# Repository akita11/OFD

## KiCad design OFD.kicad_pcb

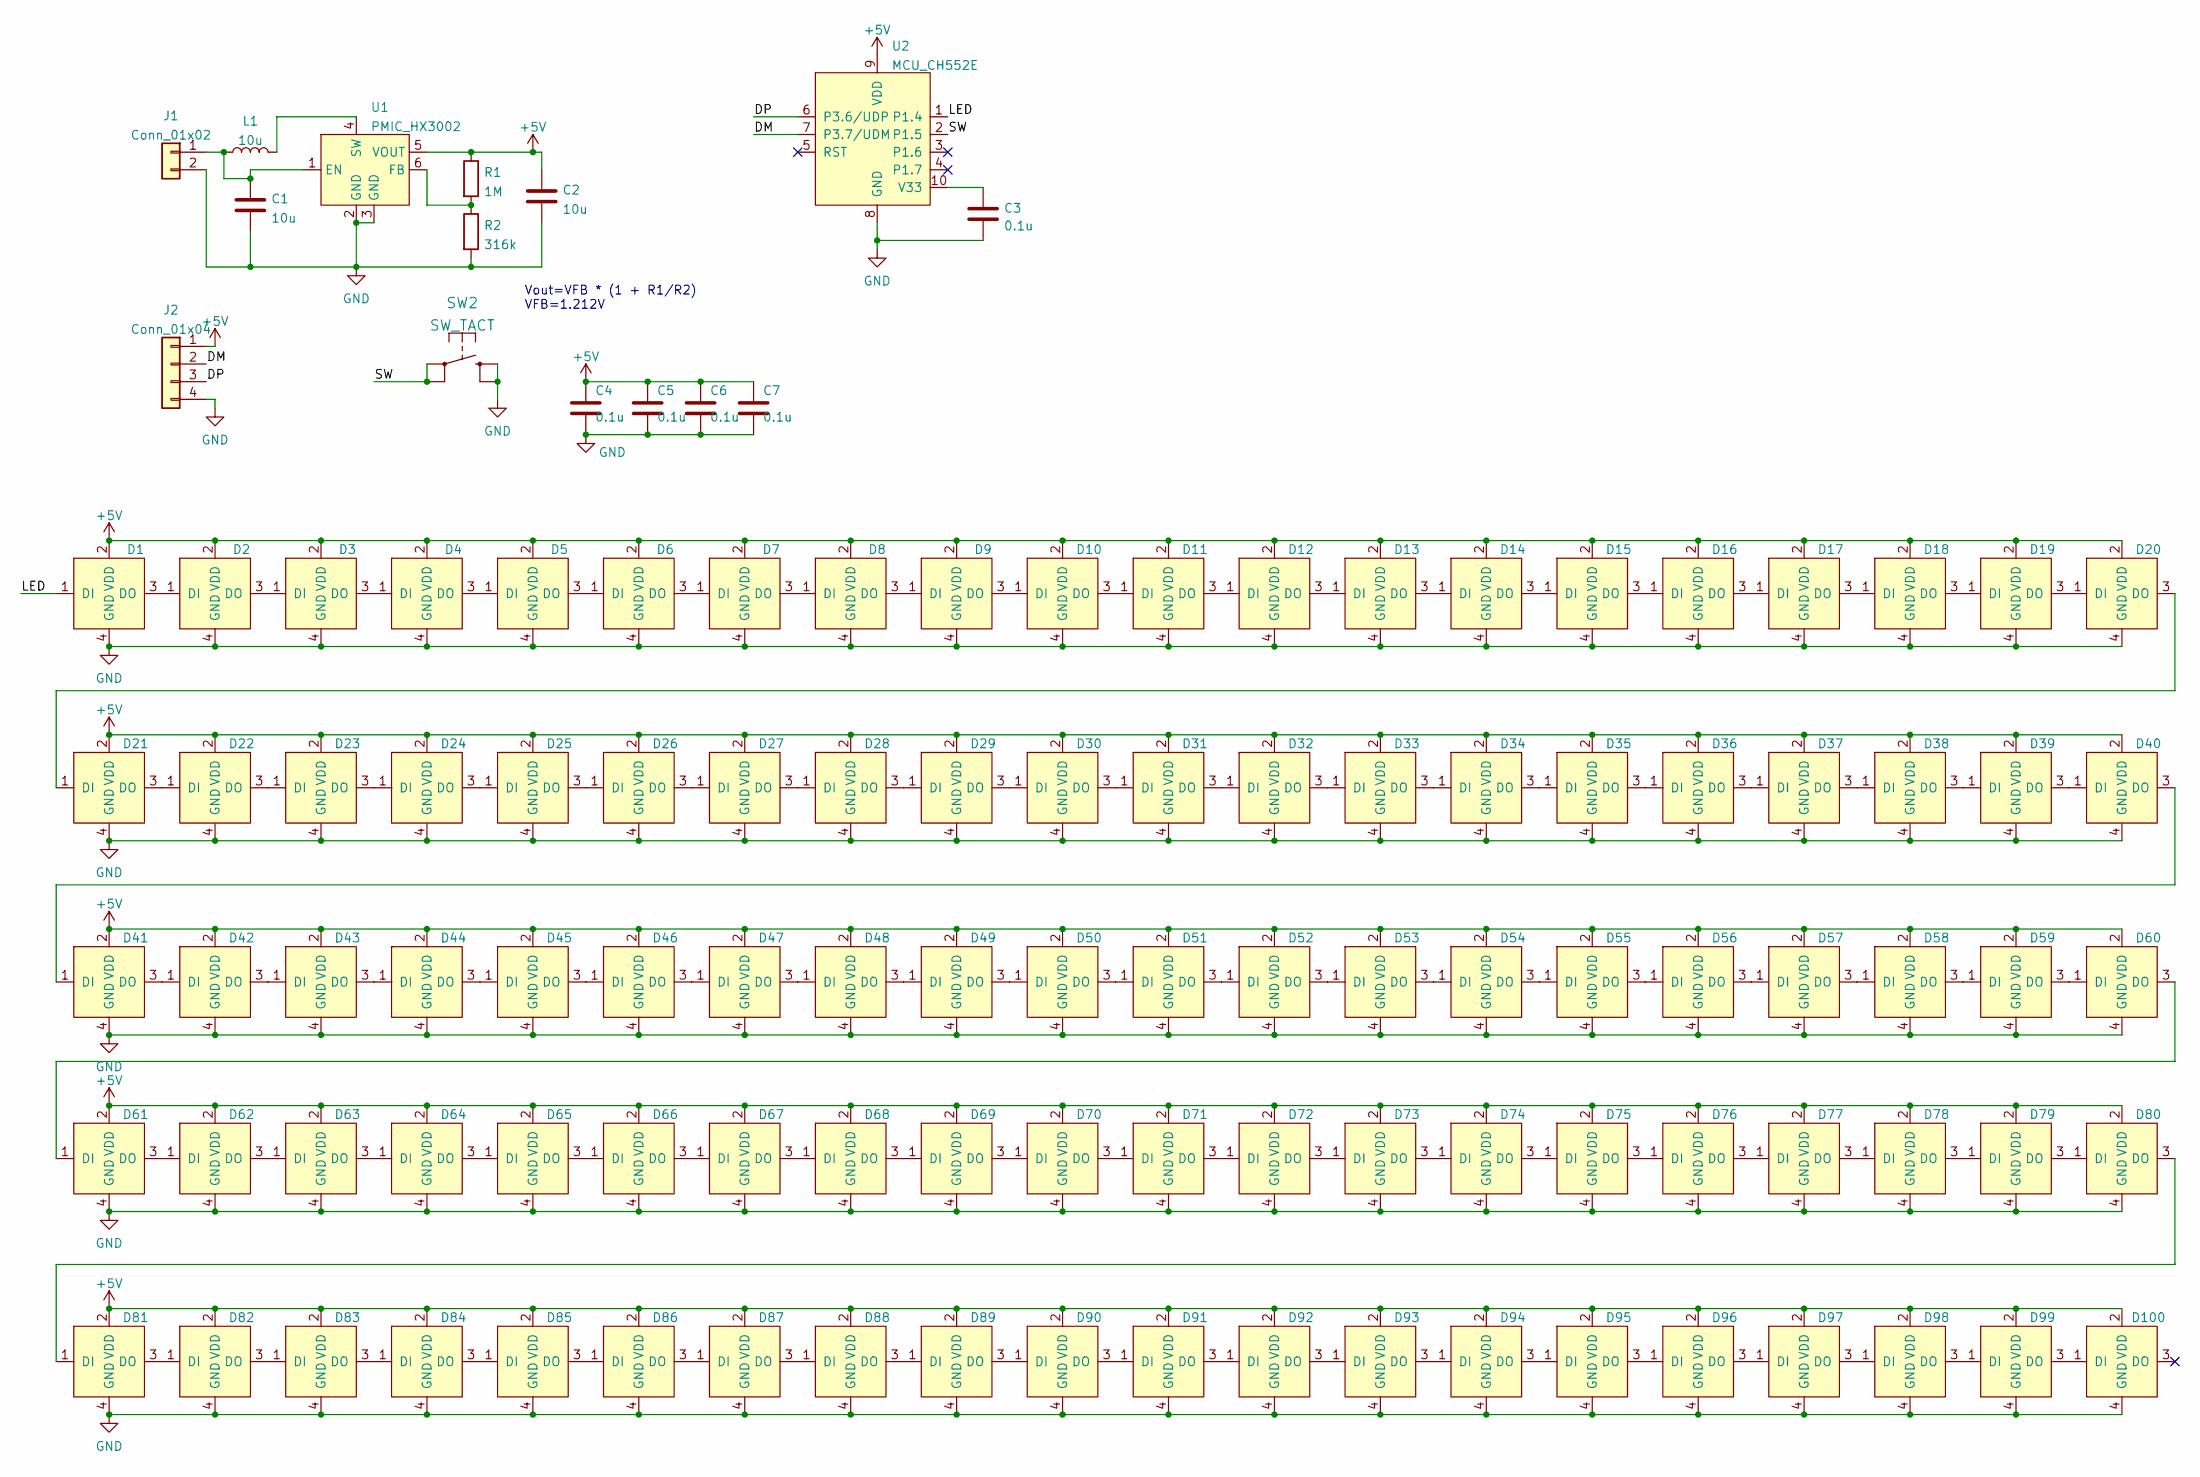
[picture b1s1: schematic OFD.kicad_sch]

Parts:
C1, C2: 10u; C_0603_1608Metric; LCSC C109454
C3, C5, C6, C7: 0.1u; C_0603_1608Metric; LCSC C14663
C4: 0.1u; C_0603_1608Metric
D1, D2, D3, D4, D5, D6, D7, D8, D9, D10, D11, D12, D13, D14, D15, D16, D17, D18, D19, D20, D21, D22, D23, D24, D25, D26, D27, D28, D29, D30, D31, D32, D33, D34, D35, D36, D37, D38, D39, D40, D41, D42, D43, D44, D45, D46, D47, D48, D49, D50, D51, D52, D53, D54, D55, D56, D57, D58, D59, D60, D61, D62, D63, D64, D65, D66, D67, D68, D69, D70, D71, D72, D73, D74, D75, D76, D77, D78, D79, D80, D81, D82, D83, D84, D85, D86, D87, D88, D89, D90, D91, D92, D93, D94, D95, D96, D97, D98, D99, D100: LED_SK6812side; LED_SK6812SIDE_A; LCSC C5378721
J1: Conn_01x02; JST_PH2_SMD; LCSC C295747
J2: Conn_01x04; PinSocket_1x04_P2.54mm_Vertical
L1: 10u; L_SMD_3x3mm; LCSC C6364790
R1: 1M; R_0603_1608Metric; LCSC C318138
R2: 316k; R_0603_1608Metric; LCSC C100961
SW2: SW_TACT; SW_SPST_B3S-1000; LCSC C2905128
U1: PMIC_HX3002; SOT-23-6; LCSC C172353
U2: MCU_CH552E; TSSOP-10_3x3mm_P0.5mm; LCSC C967938

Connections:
+5V: C2.1, C4.1, C5.1, C6.1, C7.1, D1.2 (VDD), D2.2 (VDD), D3.2 (VDD), D4.2 (VDD), D5.2 (VDD), D6.2 (VDD), D7.2 (VDD), D8.2 (VDD), D9.2 (VDD), D10.2 (VDD), D11.2 (VDD), D12.2 (VDD), D13.2 (VDD), D14.2 (VDD), D15.2 (VDD), D16.2 (VDD), D17.2 (VDD), D18.2 (VDD), D19.2 (VDD), D20.2 (VDD), D21.2 (VDD), D22.2 (VDD), D23.2 (VDD), D24.2 (VDD), D25.2 (VDD), D26.2 (VDD), D27.2 (VDD), D28.2 (VDD), D29.2 (VDD), D30.2 (VDD), D31.2 (VDD), D32.2 (VDD), D33.2 (VDD), D34.2 (VDD), D35.2 (VDD), D36.2 (VDD), D37.2 (VDD), D38.2 (VDD), D39.2 (VDD), D40.2 (VDD), D41.2 (VDD), D42.2 (VDD), D43.2 (VDD), D44.2 (VDD), D45.2 (VDD), D46.2 (VDD), D47.2 (VDD), D48.2 (VDD), D49.2 (VDD), D50.2 (VDD), D51.2 (VDD), D52.2 (VDD), D53.2 (VDD), D54.2 (VDD), D55.2 (VDD), D56.2 (VDD), D57.2 (VDD), D58.2 (VDD), D59.2 (VDD), D60.2 (VDD), D61.2 (VDD), D62.2 (VDD), D63.2 (VDD), D64.2 (VDD), D65.2 (VDD), D66.2 (VDD), D67.2 (VDD), D68.2 (VDD), D69.2 (VDD), D70.2 (VDD), D71.2 (VDD), D72.2 (VDD), D73.2 (VDD), D74.2 (VDD), D75.2 (VDD), D76.2 (VDD), D77.2 (VDD), D78.2 (VDD), D79.2 (VDD), D80.2 (VDD), D81.2 (VDD), D82.2 (VDD), D83.2 (VDD), D84.2 (VDD), D85.2 (VDD), D86.2 (VDD), D87.2 (VDD), D88.2 (VDD), D89.2 (VDD), D90.2 (VDD), D91.2 (VDD), D92.2 (VDD), D93.2 (VDD), D94.2 (VDD), D95.2 (VDD), D96.2 (VDD), D97.2 (VDD), D98.2 (VDD), D99.2 (VDD), D100.2 (VDD), J2.1, R1.1, U1.5 (VOUT), U2.9 (VDD)
/DM: J2.2, U2.7 (P3.7/UDM)
/DP: J2.3, U2.6 (P3.6/UDP)
/LED: D1.1 (DI), U2.1 (P1.4)
/SW: SW2.1, U2.2 (P1.5); also elsewhere on the board
GND: C1.2, C2.2, C3.2, C4.2, C5.2, C6.2, C7.2, D1.4 (GND), D2.4 (GND), D3.4 (GND), D4.4 (GND), D5.4 (GND), D6.4 (GND), D7.4 (GND), D8.4 (GND), D9.4 (GND), D10.4 (GND), D11.4 (GND), D12.4 (GND), D13.4 (GND), D14.4 (GND), D15.4 (GND), D16.4 (GND), D17.4 (GND), D18.4 (GND), D19.4 (GND), D20.4 (GND), D21.4 (GND), D22.4 (GND), D23.4 (GND), D24.4 (GND), D25.4 (GND), D26.4 (GND), D27.4 (GND), D28.4 (GND), D29.4 (GND), D30.4 (GND), D31.4 (GND), D32.4 (GND), D33.4 (GND), D34.4 (GND), D35.4 (GND), D36.4 (GND), D37.4 (GND), D38.4 (GND), D39.4 (GND), D40.4 (GND), D41.4 (GND), D42.4 (GND), D43.4 (GND), D44.4 (GND), D45.4 (GND), D46.4 (GND), D47.4 (GND), D48.4 (GND), D49.4 (GND), D50.4 (GND), D51.4 (GND), D52.4 (GND), D53.4 (GND), D54.4 (GND), D55.4 (GND), D56.4 (GND), D57.4 (GND), D58.4 (GND), D59.4 (GND), D60.4 (GND), D61.4 (GND), D62.4 (GND), D63.4 (GND), D64.4 (GND), D65.4 (GND), D66.4 (GND), D67.4 (GND), D68.4 (GND), D69.4 (GND), D70.4 (GND), D71.4 (GND), D72.4 (GND), D73.4 (GND), D74.4 (GND), D75.4 (GND), D76.4 (GND), D77.4 (GND), D78.4 (GND), D79.4 (GND), D80.4 (GND), D81.4 (GND), D82.4 (GND), D83.4 (GND), D84.4 (GND), D85.4 (GND), D86.4 (GND), D87.4 (GND), D88.4 (GND), D89.4 (GND), D90.4 (GND), D91.4 (GND), D92.4 (GND), D93.4 (GND), D94.4 (GND), D95.4 (GND), D96.4 (GND), D97.4 (GND), D98.4 (GND), D99.4 (GND), D100.4 (GND), J1.2, J2.4, R2.2, SW2.2, U1.2 (GND), U1.3 (GND), U2.8 (GND); also elsewhere on the board
unnamed: C1.1, J1.1, L1.1, U1.1 (EN)
unnamed: C3.1, U2.10 (V33)
unnamed: D1.3 (DO), D2.1 (DI)
unnamed: D2.3 (DO), D3.1 (DI)
unnamed: D3.3 (DO), D4.1 (DI)
unnamed: D4.3 (DO), D5.1 (DI)
unnamed: D5.3 (DO), D6.1 (DI)
unnamed: D6.3 (DO), D7.1 (DI)
unnamed: D7.3 (DO), D8.1 (DI)
unnamed: D8.3 (DO), D9.1 (DI)
unnamed: D9.3 (DO), D10.1 (DI)
unnamed: D10.3 (DO), D11.1 (DI)
unnamed: D11.3 (DO), D12.1 (DI)
unnamed: D12.3 (DO), D13.1 (DI)
unnamed: D13.3 (DO), D14.1 (DI)
unnamed: D14.3 (DO), D15.1 (DI)
unnamed: D15.3 (DO), D16.1 (DI)
unnamed: D16.3 (DO), D17.1 (DI)
unnamed: D17.3 (DO), D18.1 (DI)
unnamed: D18.3 (DO), D19.1 (DI)
unnamed: D19.3 (DO), D20.1 (DI)
unnamed: D20.3 (DO), D21.1 (DI)
unnamed: D21.3 (DO), D22.1 (DI)
unnamed: D22.3 (DO), D23.1 (DI)
unnamed: D23.3 (DO), D24.1 (DI)
unnamed: D24.3 (DO), D25.1 (DI)
unnamed: D25.3 (DO), D26.1 (DI)
unnamed: D26.3 (DO), D27.1 (DI)
unnamed: D27.3 (DO), D28.1 (DI)
unnamed: D28.3 (DO), D29.1 (DI)
unnamed: D29.3 (DO), D30.1 (DI)
unnamed: D30.3 (DO), D31.1 (DI)
unnamed: D31.3 (DO), D32.1 (DI)
unnamed: D32.3 (DO), D33.1 (DI)
unnamed: D33.3 (DO), D34.1 (DI)
unnamed: D34.3 (DO), D35.1 (DI)
unnamed: D35.3 (DO), D36.1 (DI)
unnamed: D36.3 (DO), D37.1 (DI)
unnamed: D37.3 (DO), D38.1 (DI)
unnamed: D38.3 (DO), D39.1 (DI)
unnamed: D39.3 (DO), D40.1 (DI)
unnamed: D40.3 (DO), D41.1 (DI)
unnamed: D41.3 (DO), D42.1 (DI)
unnamed: D42.3 (DO), D43.1 (DI)
unnamed: D43.3 (DO), D44.1 (DI)
unnamed: D44.3 (DO), D45.1 (DI)
unnamed: D45.3 (DO), D46.1 (DI)
unnamed: D46.3 (DO), D47.1 (DI)
unnamed: D47.3 (DO), D48.1 (DI)
unnamed: D48.3 (DO), D49.1 (DI)
unnamed: D49.3 (DO), D50.1 (DI)
unnamed: D50.3 (DO), D51.1 (DI)
unnamed: D51.3 (DO), D52.1 (DI)
unnamed: D52.3 (DO), D53.1 (DI)
unnamed: D53.3 (DO), D54.1 (DI)
unnamed: D54.3 (DO), D55.1 (DI)
unnamed: D55.3 (DO), D56.1 (DI)
unnamed: D56.3 (DO), D57.1 (DI)
unnamed: D57.3 (DO), D58.1 (DI)
unnamed: D58.3 (DO), D59.1 (DI)
unnamed: D59.3 (DO), D60.1 (DI)
unnamed: D60.3 (DO), D61.1 (DI)
unnamed: D61.3 (DO), D62.1 (DI)
unnamed: D62.3 (DO), D63.1 (DI)
unnamed: D63.3 (DO), D64.1 (DI)
unnamed: D64.3 (DO), D65.1 (DI)
unnamed: D65.3 (DO), D66.1 (DI)
unnamed: D66.3 (DO), D67.1 (DI)
unnamed: D67.3 (DO), D68.1 (DI)
unnamed: D68.3 (DO), D69.1 (DI)
unnamed: D69.3 (DO), D70.1 (DI)
unnamed: D70.3 (DO), D71.1 (DI)
unnamed: D71.3 (DO), D72.1 (DI)
unnamed: D72.3 (DO), D73.1 (DI)
unnamed: D73.3 (DO), D74.1 (DI)
unnamed: D74.3 (DO), D75.1 (DI)
unnamed: D75.3 (DO), D76.1 (DI)
unnamed: D76.3 (DO), D77.1 (DI)
unnamed: D77.3 (DO), D78.1 (DI)
unnamed: D78.3 (DO), D79.1 (DI)
unnamed: D79.3 (DO), D80.1 (DI)
unnamed: D80.3 (DO), D81.1 (DI)
unnamed: D81.3 (DO), D82.1 (DI)
unnamed: D82.3 (DO), D83.1 (DI)
unnamed: D83.3 (DO), D84.1 (DI)
unnamed: D84.3 (DO), D85.1 (DI)
unnamed: D85.3 (DO), D86.1 (DI)
unnamed: D86.3 (DO), D87.1 (DI)
unnamed: D87.3 (DO), D88.1 (DI)
unnamed: D88.3 (DO), D89.1 (DI)
unnamed: D89.3 (DO), D90.1 (DI)
unnamed: D90.3 (DO), D91.1 (DI)
unnamed: D91.3 (DO), D92.1 (DI)
unnamed: D92.3 (DO), D93.1 (DI)
unnamed: D93.3 (DO), D94.1 (DI)
unnamed: D94.3 (DO), D95.1 (DI)
unnamed: D95.3 (DO), D96.1 (DI)
unnamed: D96.3 (DO), D97.1 (DI)
unnamed: D97.3 (DO), D98.1 (DI)
unnamed: D98.3 (DO), D99.1 (DI)
unnamed: D99.3 (DO), D100.1 (DI)
unnamed: L1.2, U1.4 (SW)
unnamed: R1.2, R2.1, U1.6 (FB)

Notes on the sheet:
Vout=VFB * (1 + R1/R2) VFB=1.212V

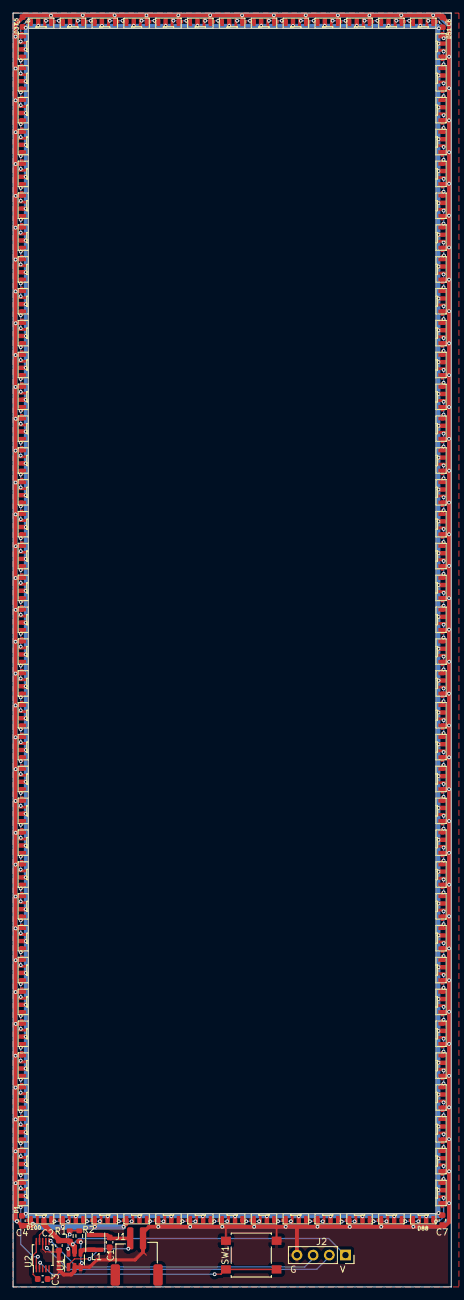
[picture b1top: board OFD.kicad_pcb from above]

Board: 2 copper layers, 68.8 x 200.0 mm, 115 parts (0 on the bottom side), 109 nets.

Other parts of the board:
SW1: SW_TACT; SW_SPST_B3S-1000

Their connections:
/SW: SW1.1; also elsewhere on the board
GND: SW1.2; also elsewhere on the board

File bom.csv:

Designator,Footprint,Quantity,Value,LCSC Part #
"C1, C2",C_0603_1608Metric,2,10u,C109454
"C3, C4, C5, C6, C7",C_0603_1608Metric,5,0.1u,C14663
"D1, D10, D100, D11, D12, D13, D14, D15, D16, D17, D18, D19, D2, D20, D21, D22, D23, D24, D25, D26, D27, D28, D29, D3, D30, D31, D32, D33, D34, D35, D36, D37, D38, D39, D4, D40, D41, D42, D43, D44, D45, D46, D47, D48, D49, D5, D50, D51, D52, D53, D54, D55, D56, D57, D58, D59, D6, D60, D61, D62, D63, D64, D65, D66, D67, D68, D69, D7, D70, D71, D72, D73, D74, D75, D76, D77, D78, D79, D8, D80, D81, D82, D83, D84, D85, D86, D87, D88, D89, D9, D90, D91, D92, D93, D94, D95, D96, D97, D98, D99",LED_SK6812SIDE_A,100,LED_SK6812side,C5378721
J1,JST_PH2_SMD,1,Conn_01x02, C295747
J2,PinSocket_1x04_P2.54mm_Vertical,1,Conn_01x04,
L1,L_SMD_3x3mm,1,10u,C6364790
R1,R_0603_1608Metric,1,1M,C318138
R2,R_0603_1608Metric,1,316k,C100961
SW2,SW_SPST_B3S-1000,1,SW_TACT,C2905128
U1,SOT-23-6,1,PMIC_HX3002,C172353
U2,TSSOP-10_3x3mm_P0.5mm,1,MCU_CH552E,C967938

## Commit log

2023-06-14 PCB outline size modified
2023-07-14 fixed D66's unconnection
2023-07-14 update gerber based on D66's unconnection fix
